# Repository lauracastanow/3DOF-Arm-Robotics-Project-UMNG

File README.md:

# 3DOF-Arm-Robotics-Project-UMNG
Este proyecto consiste en el diseño, modelado y simulación de un brazo robótico de 3 grados de libertad. En el siguiente repositorio, se incluye el desarrollo mecánico en CAD, simulación en software, código de control y una interfaz interactiva para visualizar la cinemática inversa. 

## Objetivos
### Objetivo General
Diseñar un brazo robótico integrando herramientas de hardware (CAD) y software (ROS 2, Gazebo, Python) para la posición del efector final mediante el cálculo de la cinemática y control de los actuadores en tiempo real.

### Objetivos Específicos
* Diseñar la estructura mecánica del brazo y su exportación a formato URDF.
* Modelar matemáticamente el sistema para implementar cinemática directa e inversa.
* Configurar con la simulación física en Gazebo Sim (Dynamics, colisiones e inercias).
* Establecer comunicación en tiempo real entre ROS 2 y Gazebo usando 'ros_gz_bridge'.
* Desarrollar una interfaz gráfica de usuario (GUI) interactiva para el control articular.

---

## Estructura del repositorio
El proyecto está modularizado basándose en el diagrama de bloques del sistema:

* 'Docs/' Diagramas de bloques, actas de trabajo y capturas de funcionamiento.
* 'Hardware/' Diseño CAD, mallas (meshes) y el archivo de descripción 'Ensamblee.urdf'.
* 'Simulación/' Archivos de lanzamiento ('gazebo.launch.py') y configuración del entorno virtual.
* 'Software/' Lógica de control, cinemática ('kinematics.py'), y nodo de ROS 2 conectado a la GUI ('gui.py')

---

## Descripción del sistema
El robot ("Bracito") es un manipulador que cuenta con los siguientes grados de libertad controlables:

* **Joint 1 (Base):** Rotación sobre el eje Z.
* **Joint 2 (Hombro):** Elevación del primer eslabón.
* **Joint 3 (Codo):** Elevación del segundo eslabón.
* **Joints 4, 5 y 6:** Pinza de 3 dedos configurada con plugins *Mimic* en Gazebo, permitiendo que la actuación de un solo motor cierre o abra la pinza completa de manera síncrona.

El modelo permite calcular:
* Cinemática inversa
* Posición del efector final

---

## Paquetes, Dependencias y Librerías
Para la correcta ejecución de etse proyecto, es necesario contal con el siguiente entorno:

**Entorno Base:**
* Ubuntu 24.04 (o compatible)
* [ROS 2 Jazzy] (https://docs.ros.org/en/jazzy/index.html)
*  Gazebo Sim (Harmonic)

**Librerías de Python:**
* 'rclpy' (Cliente de ROS 2 para Python)
* 'PyQt5' (Desarrollo e la interfaz gráfica)
* 'numpy' (Cálculos matriciales para la cinemática)

**Paquetes de ROS 2 utilizados:**
* 'robot_state_publisher': Para publicar el estado del robot basado en el URDF.
* 'ros_gz_sim': Para instanciar (spawn) el modelo en Gazebo.
* 'ros_gz_bridge': Para traducir los tópicos de 'JointState' / 'Float64' entre ROS 2 y Gazebo.

---

## Autoras
Proyecto desarrollado por estudiantes de Ingeniería de la Universidad Militar Nueva Granada (UMNG):
* **Laura Daniela Castaño Silva**
* **Carol Tatiana Jeréz González**

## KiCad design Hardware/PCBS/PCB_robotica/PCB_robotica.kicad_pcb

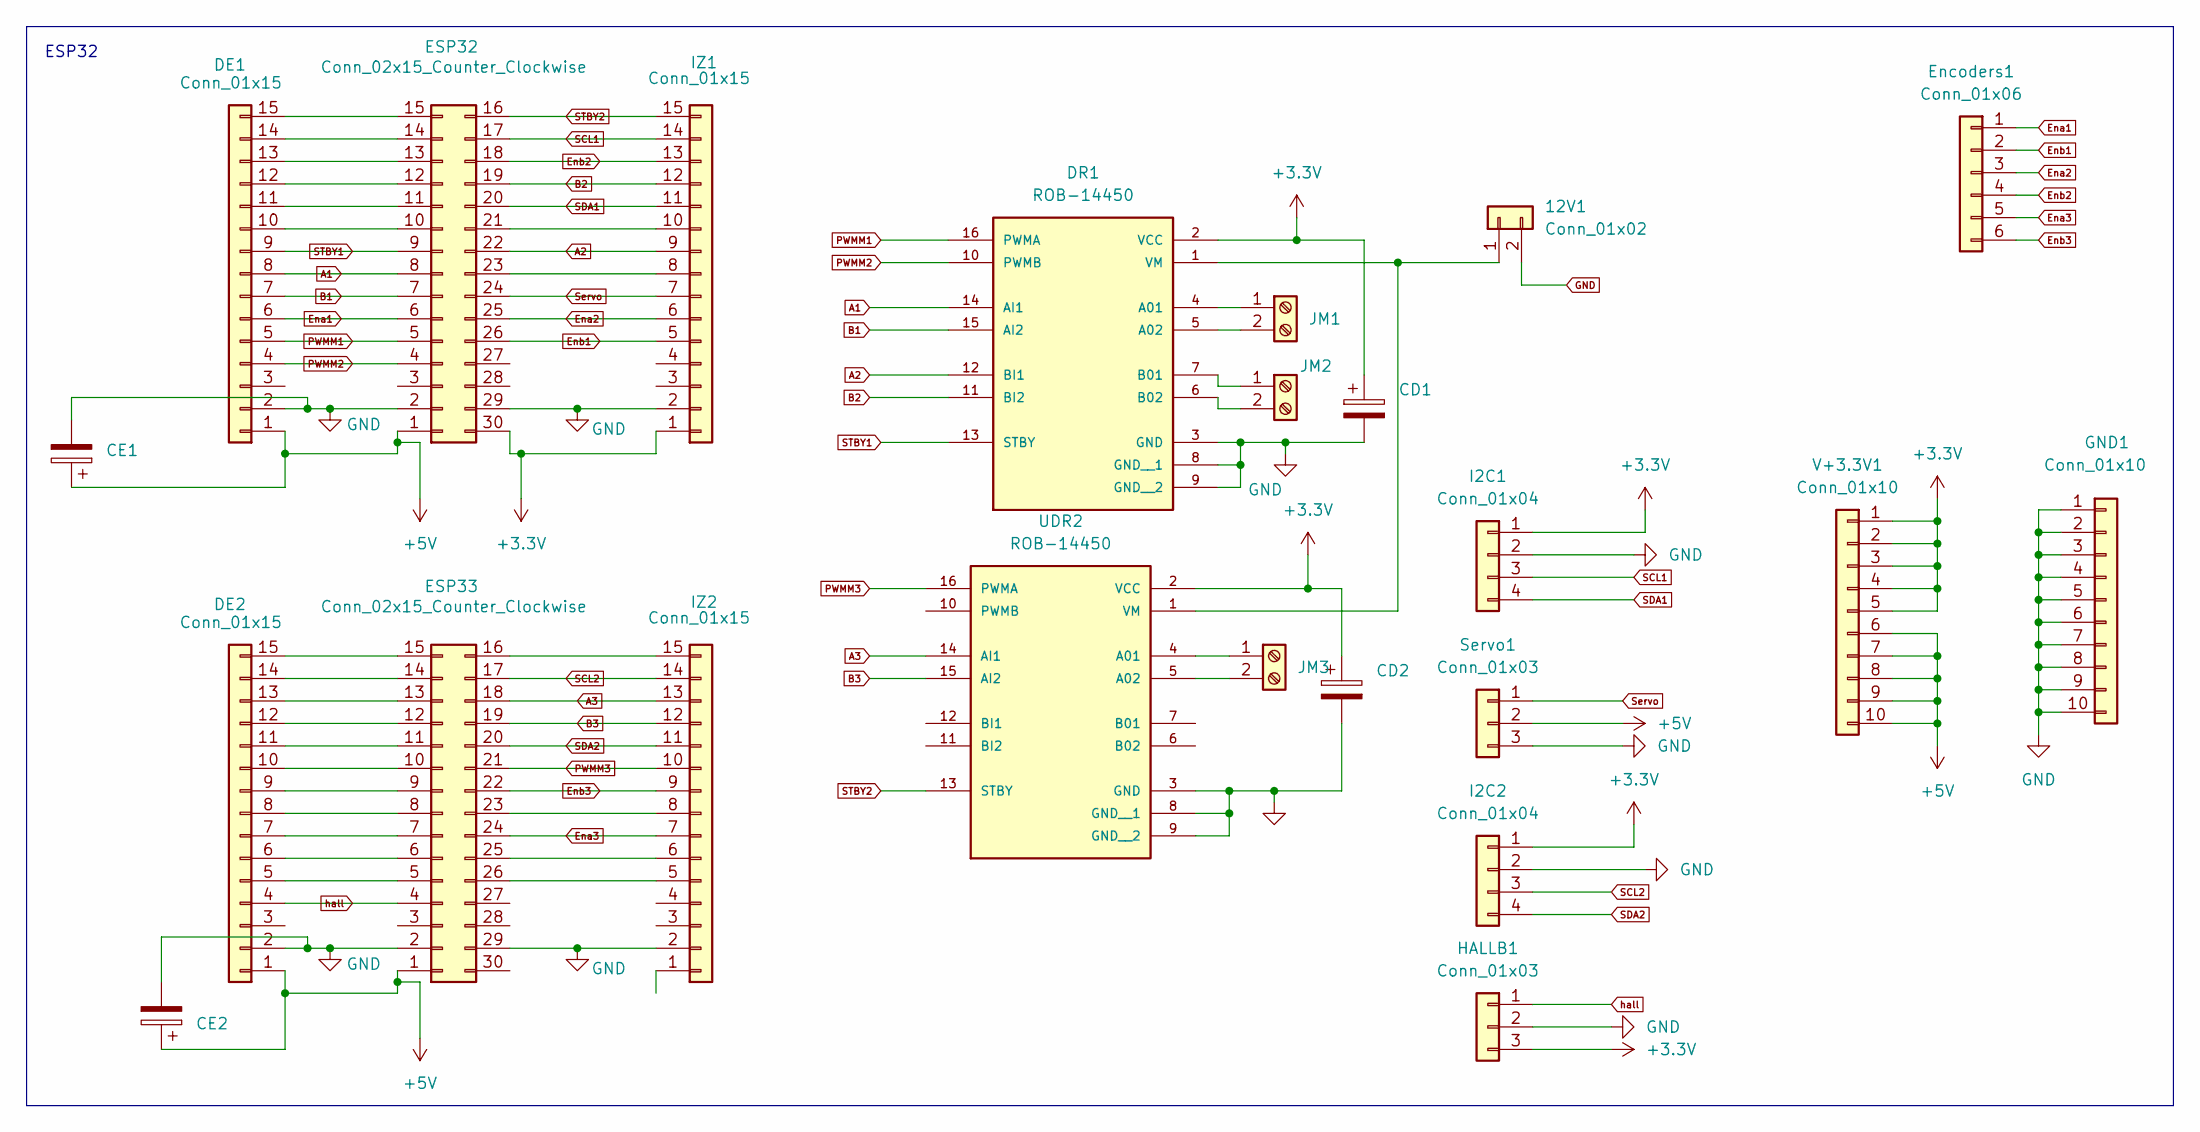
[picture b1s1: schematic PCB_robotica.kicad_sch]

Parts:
12V1: Conn_01x02; PinHeader_1x02_P2.54mm_Vertical
CD1, CD2: C_Polarized; CP_Radial_Tantal_D10.5mm_P5.00mm
CE1, CE2: C_Polarized; CP_Radial_Tantal_D10.5mm_P5.00mm
DE1, DE2: Conn_01x15; PinHeader_1x15_P2.00mm_Vertical
DR1: ROB-14450; MODULE_ROB-14450; PARTREV 11-13-17
ESP32, ESP33: Conn_02x15_Counter_Clockwise; ESP32-C3-DevKitM-1
Encoders1: Conn_01x06; PinHeader_1x06_P2.54mm_Vertical
GND1: Conn_01x10; PinHeader_1x10_P2.54mm_Vertical
HALLB1: Conn_01x03; PinHeader_1x03_P2.54mm_Vertical
I2C1, I2C2: Conn_01x04; PinHeader_1x04_P2.54mm_Vertical
IZ1, IZ2: Conn_01x15; PinHeader_1x15_P2.54mm_Vertical
JM1, JM2, JM3: Screw_Terminal_01x02; TerminalBlock_MaiXu_MX126-5.0-02P_1x02_P5.00mm
Servo1: Conn_01x03; PinHeader_1x03_P2.54mm_Vertical
UDR2: ROB-14450; MODULE_ROB-14450; PARTREV 11-13-17
V+3.3V1: Conn_01x10; PinSocket_1x10_P2.54mm_Vertical

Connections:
+3.3V: CD1.1, CD2.1, DR1.2 (VCC), ESP32.30, HALLB1.3, I2C1.1, I2C2.1, IZ1.1, UDR2.2 (VCC), V+3.3V1.1, V+3.3V1.2, V+3.3V1.3, V+3.3V1.4, V+3.3V1.5
+5V: CE1.1, CE2.1, DE1.1, DE2.1, ESP32.1, ESP33.1, Servo1.2, V+3.3V1.6, V+3.3V1.7, V+3.3V1.8, V+3.3V1.9, V+3.3V1.10
A1: DE1.8, DR1.14 (AI1), ESP32.8
A2: DR1.12 (BI1), ESP32.22, IZ1.9
A3: ESP33.18, IZ2.13, UDR2.14 (AI1)
B1: DE1.7, DR1.15 (AI2), ESP32.7
B2: DR1.11 (BI2), ESP32.19, IZ1.12
B3: ESP33.19, IZ2.12, UDR2.15 (AI2)
Ena1: DE1.6, ESP32.6, Encoders1.1
Ena2: ESP32.25, Encoders1.3, IZ1.6
Ena3: ESP33.24, Encoders1.5, IZ2.7
Enb1: ESP32.26, Encoders1.2, IZ1.5
Enb2: ESP32.18, Encoders1.4, IZ1.13
Enb3: ESP33.22, Encoders1.6, IZ2.9
GND: 12V1.2, CD1.2, CD2.2, CE1.2, CE2.2, DE1.2, DE2.2, DR1.3 (GND), DR1.8 (GND__1), DR1.9 (GND__2), ESP32.2, ESP32.29, ESP33.2, ESP33.29, GND1.1, GND1.2, GND1.3, GND1.4, GND1.5, GND1.6, GND1.7, GND1.8, GND1.9, GND1.10, HALLB1.2, I2C1.2, I2C2.2, IZ1.2, IZ2.2, Servo1.3, UDR2.3 (GND), UDR2.8 (GND__1), UDR2.9 (GND__2)
unnamed: 12V1.1, DR1.1 (VM), UDR2.1 (VM)
unnamed: DE1.10, ESP32.10
unnamed: DE1.11, ESP32.11
unnamed: DE1.12, ESP32.12
unnamed: DE1.13, ESP32.13
unnamed: DE1.14, ESP32.14
unnamed: DE1.15, ESP32.15
unnamed: DE2.5, ESP33.5
unnamed: DE2.6, ESP33.6
unnamed: DE2.7, ESP33.7
unnamed: DE2.8, ESP33.8
unnamed: DE2.9, ESP33.9
unnamed: DE2.10, ESP33.10
unnamed: DE2.11, ESP33.11
unnamed: DE2.12, ESP33.12
unnamed: DE2.13, ESP33.13
unnamed: DE2.14, ESP33.14
unnamed: DE2.15, ESP33.15
unnamed: DR1.4 (A01), JM1.1
unnamed: DR1.5 (A02), JM1.2
unnamed: DR1.7 (B01), JM2.1
unnamed: DR1.6 (B02), JM2.2
unnamed: ESP32.21, IZ1.10
unnamed: ESP32.23, IZ1.8
unnamed: ESP33.16, IZ2.15
unnamed: ESP33.23, IZ2.8
unnamed: ESP33.25, IZ2.6
unnamed: ESP33.26, IZ2.5
unnamed: JM3.1, UDR2.4 (A01)
unnamed: JM3.2, UDR2.5 (A02)
PWMM1: DE1.5, DR1.16 (PWMA), ESP32.5
PWMM2: DE1.4, DR1.10 (PWMB), ESP32.4
PWMM3: ESP33.21, IZ2.10, UDR2.16 (PWMA)
SCL1: ESP32.17, I2C1.3, IZ1.14
SCL2: ESP33.17, I2C2.3, IZ2.14
SDA1: ESP32.20, I2C1.4, IZ1.11
SDA2: ESP33.20, I2C2.4, IZ2.11
STBY1: DE1.9, DR1.13 (STBY), ESP32.9
STBY2: ESP32.16, IZ1.15, UDR2.13 (STBY)
Servo: ESP32.24, IZ1.7, Servo1.1
hall: DE2.4, ESP33.4, HALLB1.1

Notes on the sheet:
ESP32

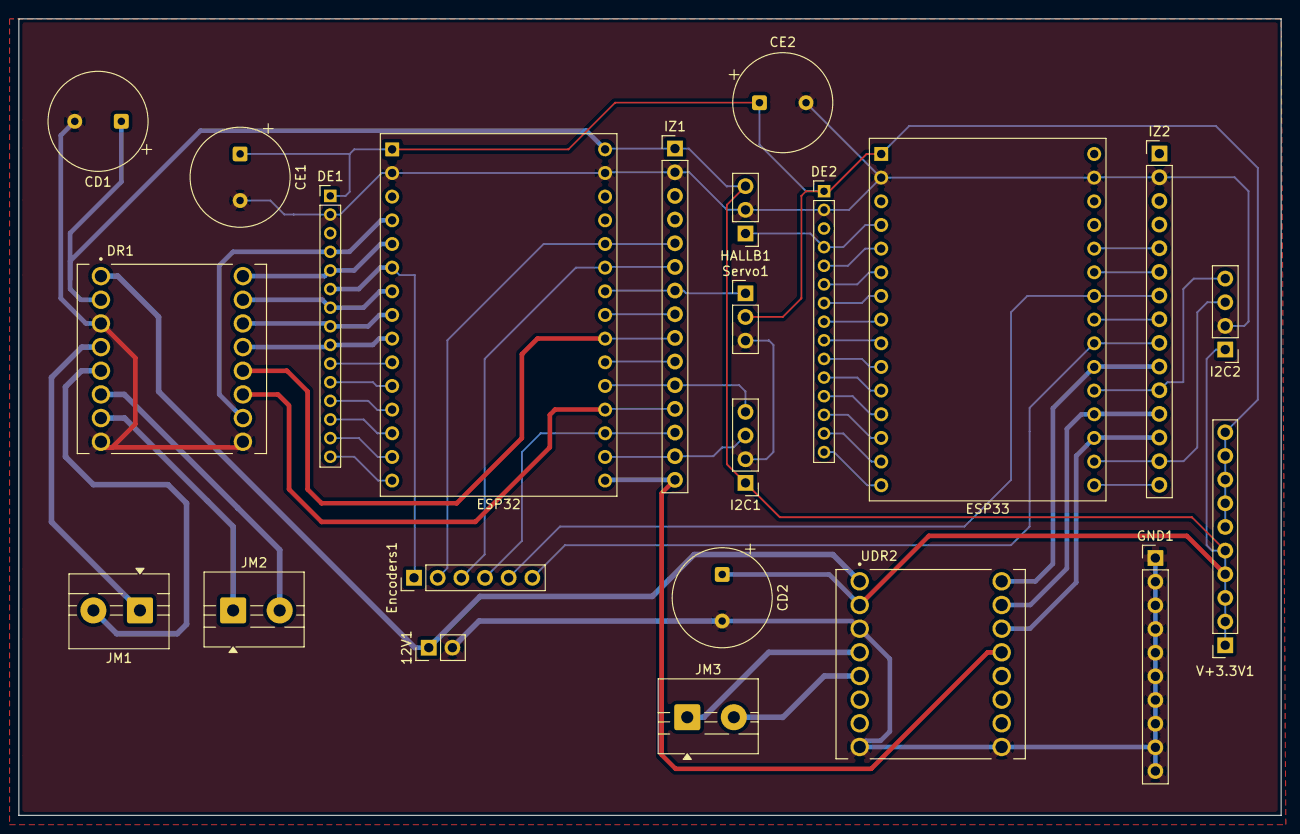
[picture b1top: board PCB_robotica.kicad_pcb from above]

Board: 2 copper layers, 135.5 x 85.5 mm, 23 parts (0 on the bottom side), 56 nets.

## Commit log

2026-03-27 Primer commit: Estructura base, CAD, simulador y GUI
2026-04-10 Actualización de códigos MATLAB, software y simulación
2026-05-28 Agregando carpetas de hardware, pinza y simulaciones
2026-05-29 Agregando carpetas de hardware y planos
